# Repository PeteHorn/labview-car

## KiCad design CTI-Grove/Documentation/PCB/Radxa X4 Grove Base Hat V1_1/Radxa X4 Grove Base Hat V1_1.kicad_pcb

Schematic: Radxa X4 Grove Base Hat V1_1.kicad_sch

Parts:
FR2: SEEEDSTUDIO-OPEN-SCH-FRAME; SEEEDSTUDIO-PCB-FRAME
J1: PIN_PITCH_2.54MM_2X3; PIN6_PITCH_2.54MM_2X3
J2, J3, J4, J5, J6, J9, J10, J11, J12, J14: 4P-2.0;320110030; 4P-2.0
SW1: 6P-2CH-2.5-9.1X3.5X3.2H-90D
U2: 2x20 2.54; RASPI_BOARD_B+HAT_DF_CF

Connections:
/3V3_GROVE: J1.2, J3.3, J4.3, J12.3, SW1.CH1A, SW1.CH2A, U2.1 (3V3@1), U2.17 (3V3@2)
/5V_GROVE: SW1.CH1B, SW1.CH2B, U2.2 (5V0@1)
/5V_Grove: U2.4 (5V0@2)
/GPIO2_Rp2040: J1.6, U2.38 (GPIO2)
/GPIO3_Rp2040: J1.5, U2.15 (GPIO3)
/GPIO4_Rp2040: J1.4, J11.2, U2.7 (GPIO4)
/GPIO5_Rp2040: J1.3, J11.1, U2.11 (GPIO5)
/GPIO6_Rp2040: J10.2, U2.13 (GPIO6)
/GPIO7_Rp2040: J10.1, U2.29 (GPIO7)
/GPIO8_Rp2040: J9.2, U2.21 (GPIO8)
/GPIO9_Rp2040: J9.1, U2.24 (GPIO9)
/GPIO10_Rp2040: U2.23 (GPIO10)
/GPIO11_Rp2040: U2.19 (GPIO11)
/GPIO12_Rp2040: J14.2, U2.31 (GPIO12)
/GPIO13_Rp2040: J14.1, U2.33 (GPIO13)
/GPIO14_Rp2040: U2.37 (GPIO14)
/GPIO15_Rp2040: U2.35 (GPIO15)
/GPIO16_Rp2040: J2.1, U2.27 (GPIO16)
/GPIO17_Rp2040: J2.2, U2.28 (GPIO17)
/GPIO18_Rp2040: J5.1, U2.26 (GPIO18)
/GPIO19_Rp2040: J5.2, U2.32 (GPIO19)
/GPIO20_Rp2040: J6.1, U2.8 (GPIO20)
/GPIO21_Rp2040: J6.2, U2.10 (GPIO21)
/GPIO22_Rp2040: U2.16 (GPIO22)
/GPIO23_Rp2040: U2.12 (GPIO23)
/GPIO24_Rp2040: U2.22 (GPIO24)
/GPIO25_Rp2040: U2.40 (GPIO25)
/GPIO26_Rp2040: J4.2, J12.1, U2.36 (GPIO26)
/GPIO27_Rp2040: J3.2, J4.1, U2.18 (GPIO27)
/GPIO28_Rp2040: J3.1, U2.3 (GPIO28)
/GPIO29_Rp2040: U2.5 (GPIO29)
/NC: J12.2
/VCC: J2.3, J5.3, J6.3, J9.3, J10.3, J11.3, J14.3, SW1.COM1, SW1.COM2
GND_POWER: J1.1, J2.4, J3.4, J4.4, J5.4, J6.4, J9.4, J10.4, J11.4, J12.4, J14.4, U2.6 (GND@1), U2.9 (GND@2), U2.14 (GND@3), U2.20 (GND@4), U2.25 (GND@5), U2.30 (GND@6), U2.34 (GND@7), U2.39 (GND@8)

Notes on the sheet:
ADC (A2)
ADC (A1)
SCL
Vincent
UART0
GPIO (D20)
ADC (A0)
2018/7/24
Initial release
GPIO (D16)
UART1
I2C1
SDA
v1.0
GPIO (D18)
I2C0

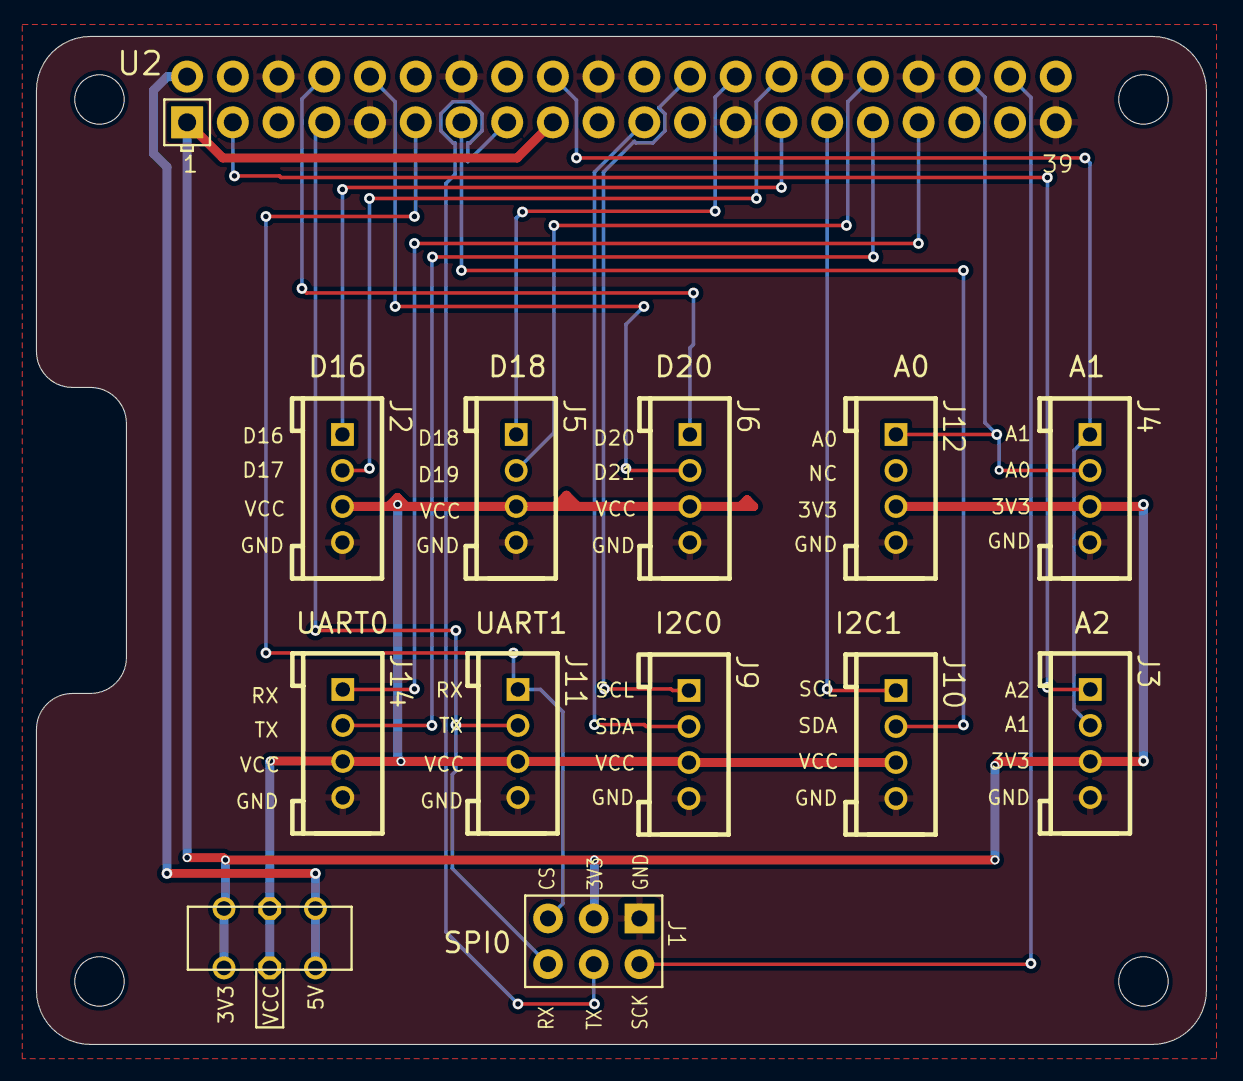
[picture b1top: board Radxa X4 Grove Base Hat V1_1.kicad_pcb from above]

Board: 2 copper layers, 65.0 x 56.0 mm, 14 parts (0 on the bottom side), 23 nets.

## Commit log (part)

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2026-05-17 added in the cti-grove examples and built a small poc for the car, motor's working forward direction only. Started building an actor for motor control
2026-05-18 rebuilt the firmware so that the odd numbered channels work - now have the motor test working
2026-05-19 line tracking poc working, module not yet working

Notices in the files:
CTI-Grove/Documentation/PCB/Radxa X4 Grove Base Hat V1_1/Radxa X4 Grove Base Hat V1_1.kicad_sch:
CC-BY-SA
parts and their libraries:
This work is licensed under the Creative Commons Attribution 4.0 International License.
To view a copy of this license,visit:
http://creativecommons.org/licenses/by-sa/4.0
